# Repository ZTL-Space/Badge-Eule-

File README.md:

# Entnervte Eule - Lötanleitung

## Einleitung
Die Entnervte Eule ist ein einfacher Bausatz zum selber Zusammenlöten, der im ZTL, dem Zentrum für Technikkultur in Landau, designed wurde.

Die Eule gibt es in 12 verschiedenen Varianten zur Wahl.
Die Platine ist entweder Weiß/Silbern oder Schwarz/Gold.
Die LEDs, welche die Augen darstellen, gibt es in Rot, Gelb, Grün, Blau, langsamer Farbwechsel und schneller Farbwechsel.

## Auspacken

Die Bauteile kommen in einem wiederverschließbaren Beutel, den ihr am Ende mit nach Hause nehmen oder uns zurück geben könnt. Dann wird er wiederverwendet.

<div style="page-break-after: always;"></div>

## Die Bauteile

Folgende Bauteile sollten in der Tüte sein:

- Platine
- Papiergurt mit 2 Widerständen
- Plastikgurt mit 2 LEDs
- Schiebeschalter
- Knopfzellenhalter
- Knopfzelle

<div style="page-break-after: always;"></div>

## Widerstände - R1 und R2

### Auspacken

Zuerst musst du die beiden Widerstände aus dem Papiergurt befreien, indem du mit der Pinzette den Plastikfilm abziehst. Mach das am besten über dem Holzbrett, sodass die Widerstände nicht verloren gehen, sollten sie herunterfallen.

<div style="page-break-after: always;"></div>

### Vorverzinnen

Nun musst du eins der beiden Pads von R1 vorverzinnen. Dazu setzt du die Spitze des Lötkolbens auf das Pad und fügst Lötzinn hinzu bis es schmilzt und sich ein kleiner Hügel auf dem Pad bildet. 

Bitte lass das zweite Pad noch frei.

Das Gleiche machst du bei R2.

<div style="page-break-after: always;"></div>

### Bauteile platzieren

Nimm die Pinzette in deine schwache Hand und den Lötkolben in die starke. Du musst das Lötzinn vom Vorverzinnen auf einem der Pads erneut aufschmelzen und einen Widerstand mit der Pinzette von der Seite hineinschieben. Ist der Widerstand korrekt platziert, nimmst du den Lötkolben weg und wartest ein paar Sekunden, bis das Lötzinn wieder fest ist. Dann kannst du das Bauteil mit der Pinzette loslassen.

Das Gleiche wiederholst du für den zweiten Widerstand.

<div style="page-break-after: always;"></div>

### Bauteile festlöten

Jetzt sind die Widerstände nur auf einer Seite verbunden. Mit dem Lötzinn und dem Lötkolben musst du auch noch die andere Seite verlöten.

<div style="page-break-after: always;"></div>

## LEDs - D1 und D2

### Auspacken

Nun musst du die beiden LEDs aus dem Plastikgurt heraus holen.

Die LEDs haben einen Pfeil, der anzeigt in welcher Orientierung sie aufgelötet werden müssen. Je nach Farbe der LED kann der Pfeil unterschiedlich aussehen.

<div style="page-break-after: always;"></div>

### Vorverzinnen

Verzinne ein Pad von D1.

Das Gleiche machst du bei D2.

<div style="page-break-after: always;"></div>

### Bauteile platzieren

Da wir die LEDs "auf dem Kopf" auflöten, geht das ein bisschen schwieriger als bei den Widerständen, vom Prinzip ist es aber das Gleiche. Befestige zu erst D1. **Achte darauf, dass der Pfeil auf der LED in die gleiche Richtung zeigt wie der Pfeil auf der Platine, in Richtung Kopf der Eule.**

Das Gleiche wiederholst du für D2.

<div style="page-break-after: always;"></div>

### Bauteile festlöten

Verlöte jetzt die andere Seite von D1 und D2

<div style="page-break-after: always;"></div>

## Schiebeschalter - SW1

### Vorverzinnen

Verzinne exakt nur ein Pad von SW1. Wirklich. **Nur eins!**

### Bauteil platzieren

Nimm den Schalter wie gehabt mit der Pinzette. Schmelze das Lötzinn auf und schiebe den Schalter mit einem Beinchen in das flüssige Lötzinn.

### Bauteil festlöten

Befestige die restlichen Beinchen

<div style="page-break-after: always;"></div>

## Knopfzellenhalter - BT1

### Vorverzinnen

Verzinne ein Pad des Knopfzellenhalters

### Bauteil platzieren

Den Knopfzellenhalter kannst du mit der Hand platzieren.
Drücke mit der Lötkolbenspitze auf das Metallfähnchen bis das darunter liegende Lötzinn aufgeschmolzen ist und der Halter einsinkt.
**Achte darauf, den Halter richtig herum anzulöten. Eine Ecke des Halters ist abgeschrägt. Diese Schräge kannst du auch auf dem Bestückungsdruck sehen.**

### Bauteil festlöten

Verlöte die zweite Lötfahne des Knopfzellenhalters.

<div style="page-break-after: always;"></div>

## Knopfzelle

### Auspacken

Entferne das Kreppband von der Knopfzelle.

### Einlegen

Lege die Knopfzelle mit der glatten Seite nach oben in den Knopfzellenhalter ein. Achte darauf, dass die Knopfzelle **unter** den kurzen Metallkontakten ist und drücke sie mit dem Daumen ein, bis sie einrastet.

<div style="page-break-after: always;"></div>

### Anschalten und ausprobieren

Wenn du den Schalter auf On stellst, sollten beide LEDs leuchten.

Glückwunsch! Wirf den Müll in die Müllbehälter und lege die Werkzeuge wieder auf das Brett.

Sollte die Eule nicht funktionieren, sag uns bescheid und wir helfen dir den Fehler zu finden.

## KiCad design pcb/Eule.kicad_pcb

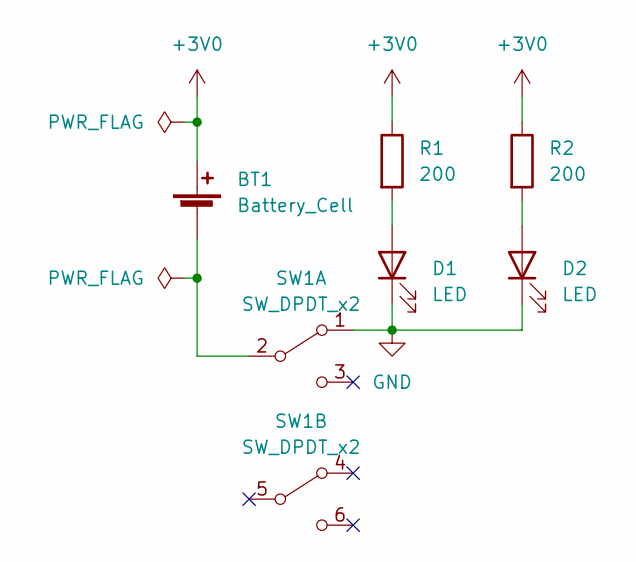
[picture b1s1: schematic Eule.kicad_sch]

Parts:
BT1: Battery_Cell; BatteryHolder_Keystone_1060_1x2032
D1, D2: LED; LED_1210_3225Metric_Pad1.42x2.65mm_HandSolder
R1, R2: 200; R_1210_3225Metric_Pad1.30x2.65mm_HandSolder
SW1: SW_DPDT_x2; MSS22D18G2

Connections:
+3V0: BT1.1 (+), R1.1, R2.1
GND: D1.1 (K), D2.1 (K), SW1.1 (A)
unnamed: BT1.2 (-), SW1.2 (B)
unnamed: D1.2 (A), R1.2
unnamed: D2.2 (A), R2.2

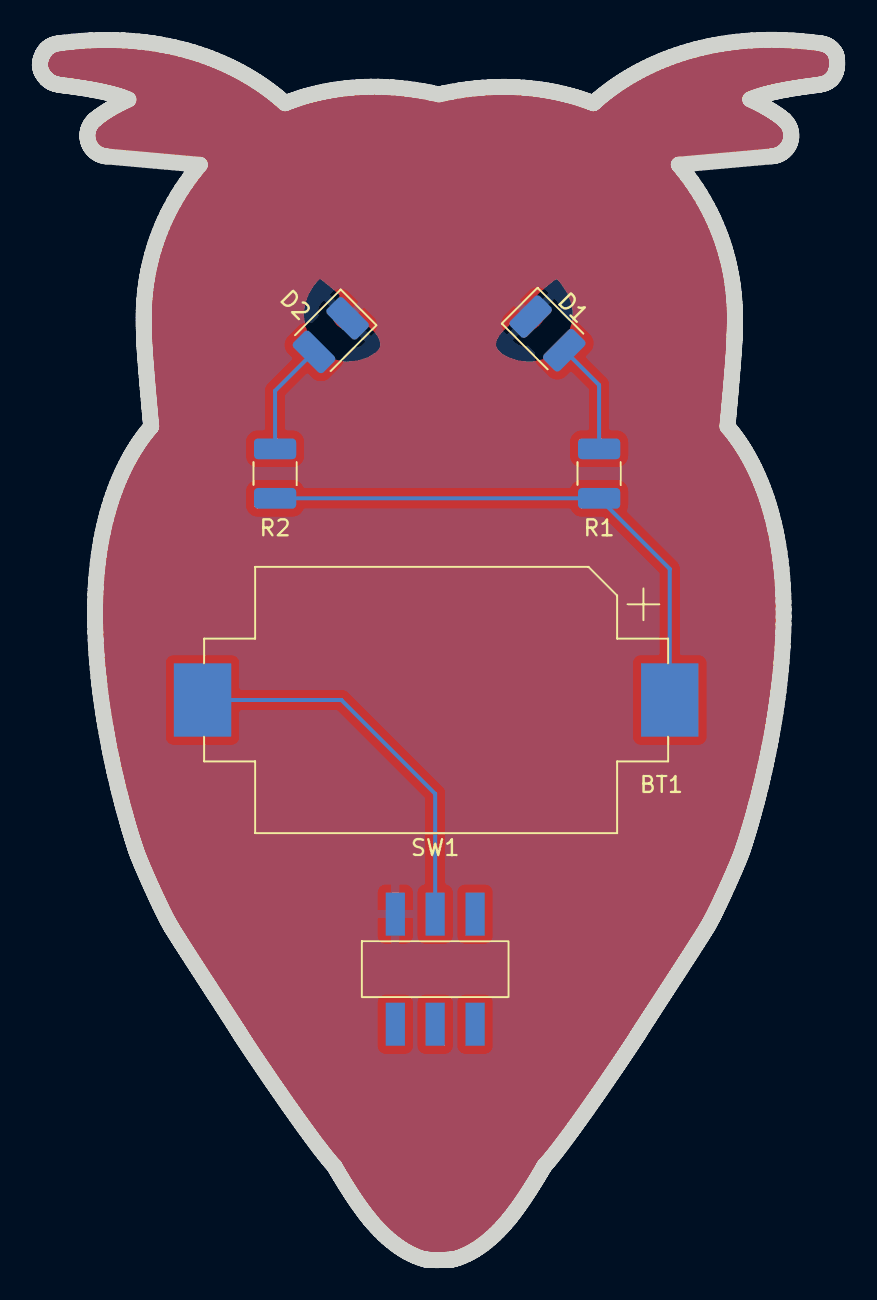
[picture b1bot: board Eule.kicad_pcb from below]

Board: 2 copper layers, 50.0 x 76.5 mm, 6 parts (6 on the bottom side), 5 nets.

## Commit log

2023-01-13 generated gerber v1.0
2023-01-13 fixed eyes
2023-01-15 added ibom
2023-02-02 v2.0
    changed switch
    increased footprint for batterie holder
    text
2023-02-02 update bom
2023-02-21 footprint enlarged Text changes LED arrow
2023-04-03 add doc
2024-03-22 add QR-Code-Sheet
2024-03-22 first step converting instructions pdf to mardown
2024-03-22 add information for qr code generator which is not totally shit
2024-03-25 add tray insert
2024-03-28 Update README.md
    Anleitung Text umgeschrieben
2024-03-28 Bilder für die Doku
    Bilder für die Doku hinzugefügt
2024-03-28 added images to readme and minor corrections
2024-04-04 Anleitung(2) für Ausdrucke
2024-05-19 Update Doku - Einlegen der Batterie
2024-06-29 separate qr code sheets for black and new design for white
2025-05-27 change name of README to README_old
2025-05-27 new instructions
2025-05-28 Update README.md
    Textkorrekturen Rechtschreibung
2025-05-30 readme fixes
2025-06-04 Update README.md
    IMG_0158.JPG war irrtümlich doppelt eingebunden
2025-06-11 readme improvement
2025-06-11 brighten pictures
2025-06-11 optimize readme for print
2025-06-11 add readme as html to print
2025-06-11 minor readme corrections and pdf export
